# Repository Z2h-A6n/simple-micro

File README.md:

# Simple Micro
KiCad files for a simple microcontroller breakout board. Nearly a clone of the
[Sparkfun Pro Micro](https://www.sparkfun.com/products/12640)

## Overview
This is a simple breakout board for the Atmel ATMega32u4 microcontroller that is
very closely based on the Pro Micro by Sparkfun Electonics. The primary
differences between the Pro Micro and the Simple Micro are:
- The Pro Micro is physically smaller.
- The Simple Micro breaks out a few more of the I/O pins on the ATMega.
- The USB pins on the Simple Micro are broken out to through-hole pads as well as a surface-mount USB receptacle.
- The Simple Micro is cheaper (as of this writing).
  - e.g. Making 3 Simple Micros with boards from OSH Park and components from DigiKey cost $34. See the [example parts list](parts-list.txt).
- The Pro Micro comes pre-built.
- The Pro Micro was made by people who presumably know what they are doing, while the Simple Micro was designed by someone with no formal training in microcontroller use or PCB design.

## Files in this repo
Most of the files in the repo are KiCad project files. The other files are:
- assembly.pdf
  - A pdf showing the exposed pads on the bare PCB marked up with component labels to help with assembling the board.
- README.md
  - This document.

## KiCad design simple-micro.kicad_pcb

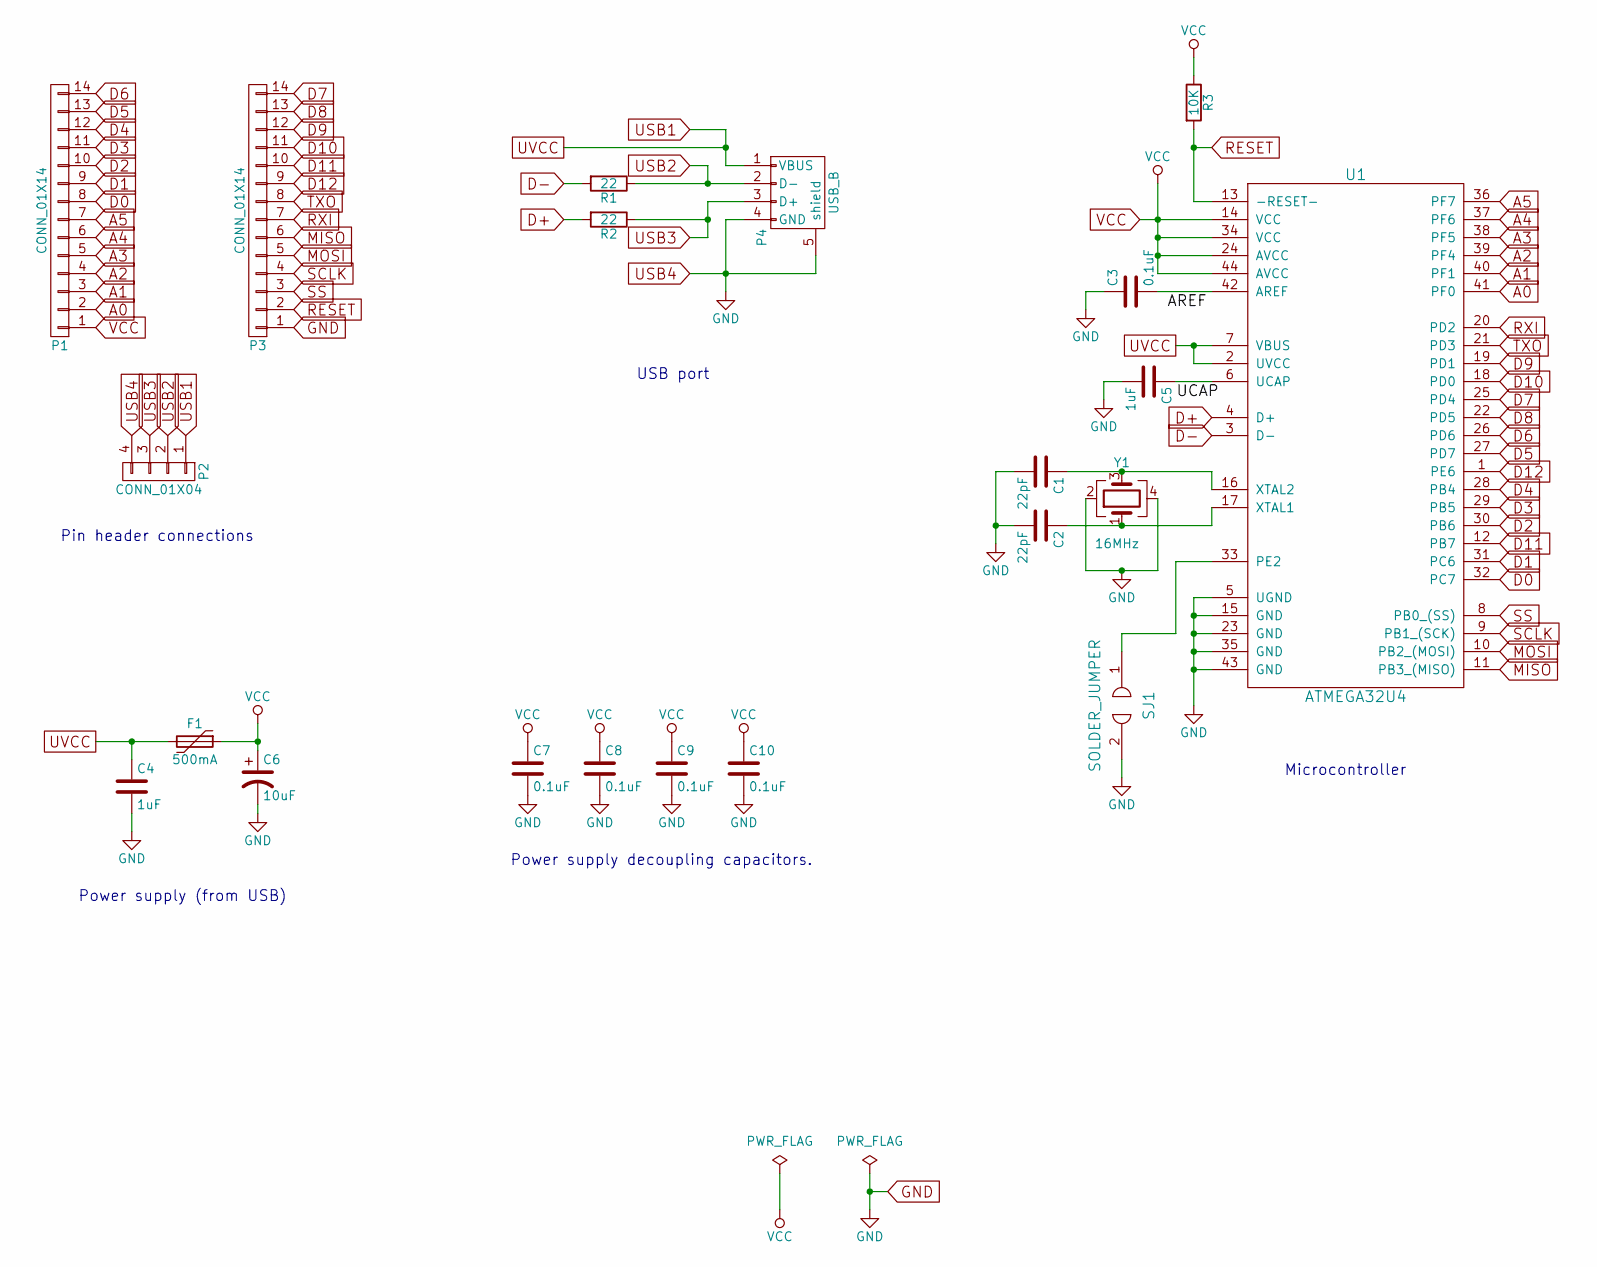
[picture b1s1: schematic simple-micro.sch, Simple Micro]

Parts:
C1, C2: 22pF; C_0603
C3, C7, C8, C9, C10: 0.1uF; C_0603
C4, C5: 1uF; C_0603
C6: 10uF; Tantalum_Case-A_EIA-3216-18_Reflow
F1: 500mA; Fuse_SMD1206_Reflow
P1, P3: CONN_01X14; Pin_Header_Straight_1x14
P2: CONN_01X04; Pin_Header_Straight_1x04
P4: USB_B; USB_MICROB_SMD-TH
R1, R2: 22; R_0603
R3: 10K; R_0603
SJ1: SOLDER_JUMPER; Solder_Jumper
U1: ATMEGA32U4; TQFP-44_10x10mm_Pitch0.8mm
Y1: 16MHz; Crystal_SMD_3.2X2.5_4PAD

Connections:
A0: P1.2, U1.41 (PF0)
A1: P1.3, U1.40 (PF1)
A2: P1.4, U1.39 (PF4)
A3: P1.5, U1.38 (PF5)
A4: P1.6, U1.37 (PF6)
A5: P1.7, U1.36 (PF7)
D0: P1.8, U1.32 (PC7)
D1: P1.9, U1.31 (PC6)
D2: P1.10, U1.30 (PB6)
D3: P1.11, U1.29 (PB5)
D4: P1.12, U1.28 (PB4)
D5: P1.13, U1.27 (PD7)
D6: P1.14, U1.26 (PD6)
D7: P3.14, U1.25 (PD4)
D8: P3.13, U1.22 (PD5)
D9: P3.12, U1.19 (PD1)
D10: P3.11, U1.18 (PD0)
D11: P3.10, U1.12 (PB7)
D12: P3.9, U1.1 (PE6)
D+: R2.2, U1.4 (D+)
D-: R1.2, U1.3 (D-)
GND: C1.2, C2.2, C3.1, C4.2, C5.2, C6.2, C7.2, C8.2, C9.2, C10.2, P2.4, P3.1, P4.4 (GND), P4.5 (shield), SJ1.2, U1.5 (UGND), U1.15 (GND), U1.23 (GND), U1.35 (GND), U1.43 (GND), Y1.2, Y1.4
MISO: P3.6, U1.11 (PB3_(MISO))
MOSI: P3.5, U1.10 (PB2_(MOSI))
unnamed: C1.1, U1.16 (XTAL2), Y1.3
unnamed: C2.1, U1.17 (XTAL1), Y1.1
unnamed: C3.2, U1.42 (AREF)
unnamed: C5.1, U1.6 (UCAP)
unnamed: SJ1.1, U1.33 (PE2)
RESET: P3.2, R3.2, U1.13 (-RESET-)
RXI: P3.7, U1.20 (PD2)
SCLK: P3.4, U1.9 (PB1_(SCK))
SS: P3.3, U1.8 (PB0_(SS))
TXO: P3.8, U1.21 (PD3)
USB1: C4.1, F1.2, P2.1, P4.1 (VBUS), U1.2 (UVCC), U1.7 (VBUS)
USB2: P2.2, P4.2 (D-), R1.1
USB3: P2.3, P4.3 (D+), R2.1
VCC: C6.1, C7.1, C8.1, C9.1, C10.1, F1.1, P1.1, R3.1, U1.14 (VCC), U1.24 (AVCC), U1.34 (VCC), U1.44 (AVCC)

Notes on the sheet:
Power supply decoupling capacitors.
Power supply (from USB)
Pin header connections
USB port
Microcontroller

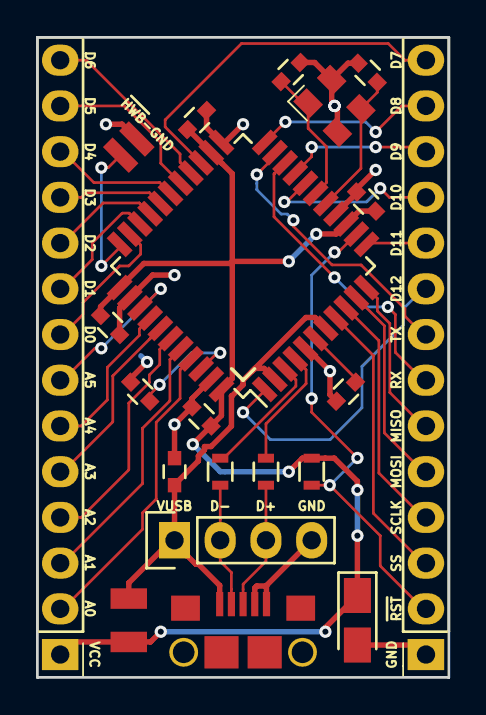
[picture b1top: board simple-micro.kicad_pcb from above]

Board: 2 copper layers, 22.9 x 35.6 mm, 21 parts (0 on the bottom side), 38 nets.

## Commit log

2017-05-30 Initial commit. v1.0
    This is the first version sent to the fab.
2017-06-01 removed some extraneous files
2017-06-01 tracking *.pdf with git-lfs
2017-06-01 added assembly notes
2017-06-01 added README.md
2017-06-01 Fixed formatting for github.
2017-06-01 added an example parts list

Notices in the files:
simple-micro.kicad_pcb:
License: GPLv3
